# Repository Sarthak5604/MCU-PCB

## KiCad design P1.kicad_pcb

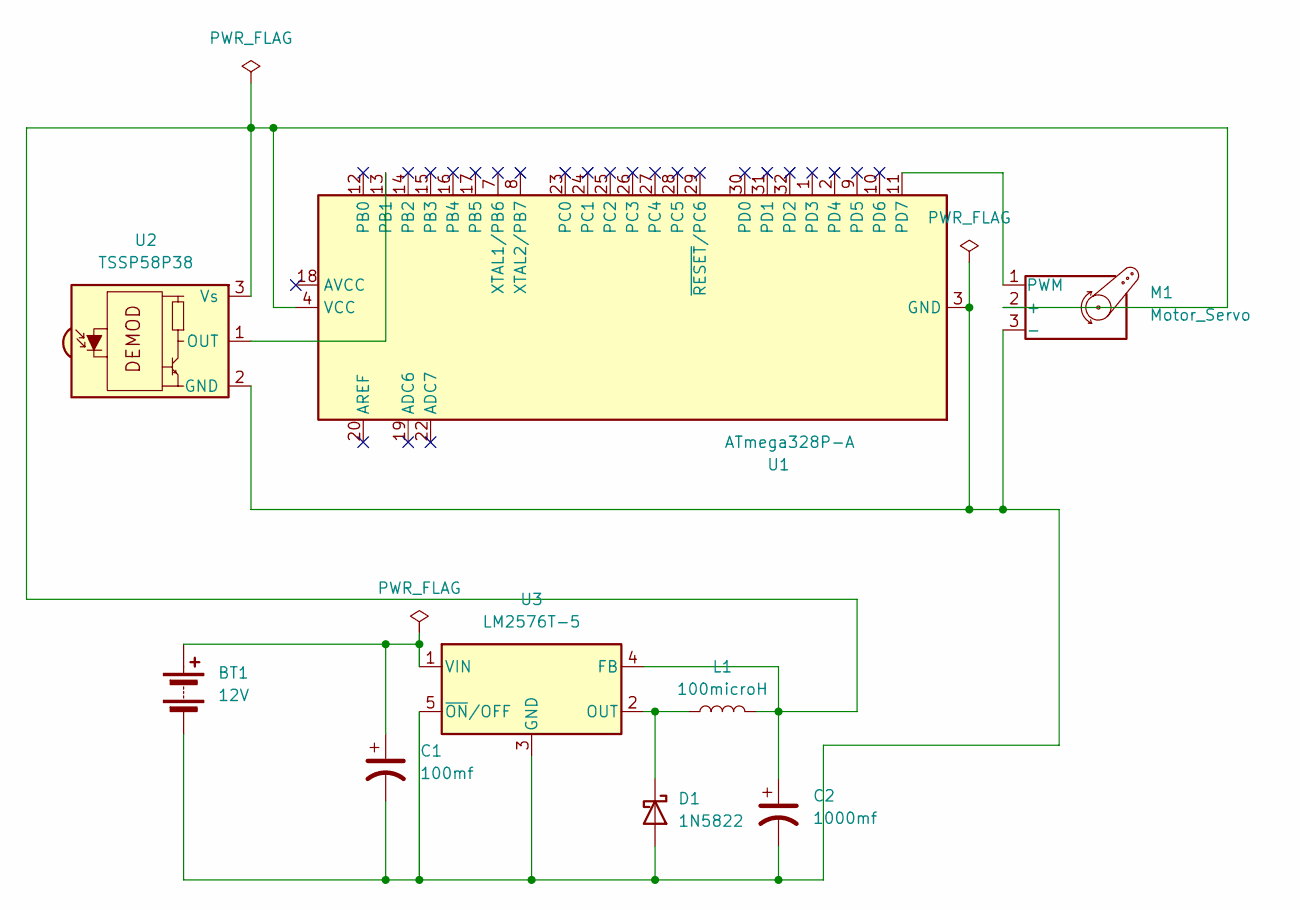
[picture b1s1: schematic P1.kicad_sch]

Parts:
BT1: 12V; PinHeader_1x02_P2.54mm_Vertical
C1: 100mf; CP_Axial_L10.0mm_D4.5mm_P15.00mm_Horizontal
C2: 1000mf; CP_Axial_L10.0mm_D4.5mm_P15.00mm_Horizontal
D1: 1N5822; D_DO-201AD_P15.24mm_Horizontal
L1: 100microH; L_Axial_L5.0mm_D3.6mm_P10.00mm_Horizontal_Murata_BL01RN1A2A2
M1: Motor_Servo; PinHeader_1x03_P2.54mm_Vertical
U1: ATmega328P-A; TQFP-32_7x7mm_P0.8mm
U2: TSSP58P38; Vishay_MINICAST-3Pin
U3: LM2576T-5; TO-220-5_Vertical

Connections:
unnamed: BT1.1 (+), C1.1, U3.1 (VIN)
unnamed: BT1.2 (-), C1.2, C2.2, D1.2 (A), M1.3 (-), U1.3 (GND), U1.5 (GND), U1.21 (GND), U2.2 (GND), U3.3 (GND), U3.5 (~ON/OFF)
unnamed: D1.1 (K), L1.1, U3.2 (OUT)
unnamed: C2.1, L1.2, M1.2 (+), U1.4 (VCC), U1.6 (VCC), U2.3 (Vs), U3.4 (FB)
unnamed: M1.1 (PWM), U1.11 (PD7)
unnamed: U1.13 (PB1), U2.1 (OUT)

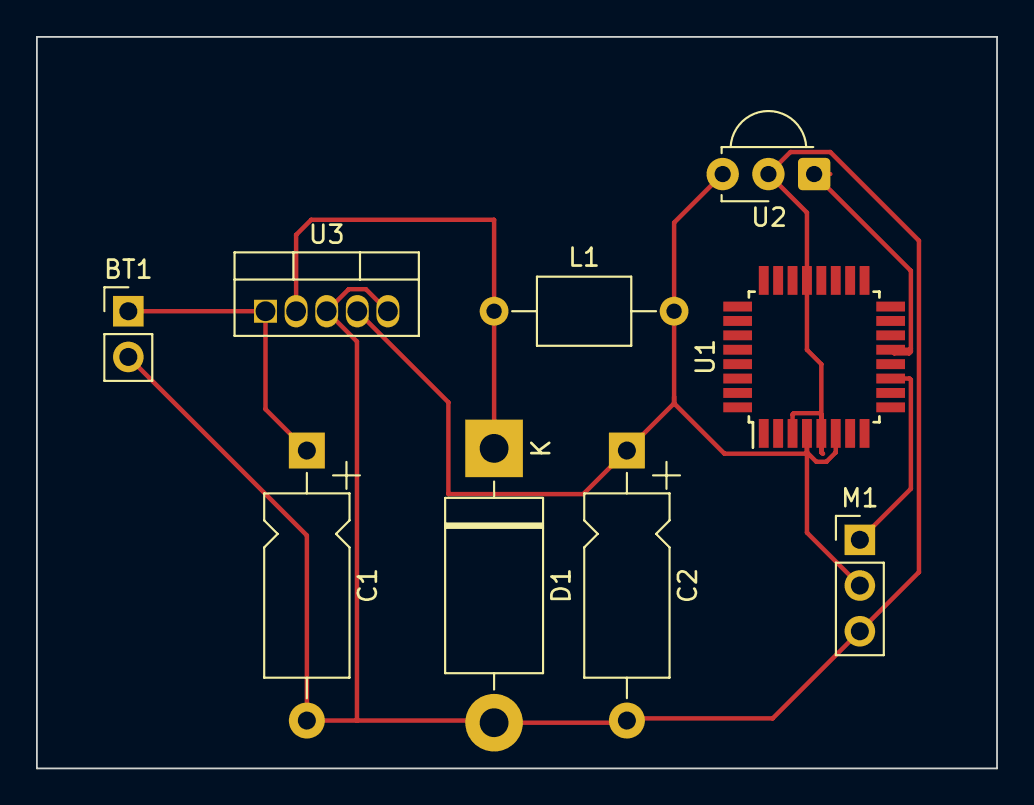
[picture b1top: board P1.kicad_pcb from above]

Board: 2 copper layers, 53.3 x 40.6 mm, 9 parts (0 on the bottom side), 6 nets.

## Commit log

2024-02-04 Create Stage 1
2024-02-04 Update Stage 1
2024-02-04 Create Stage 2
2024-02-04 Update Stage 2
2024-02-04 Create Stage 3
